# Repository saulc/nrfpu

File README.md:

# nrfpu
eagle pcb for atmega328p pu and nrf24l01+

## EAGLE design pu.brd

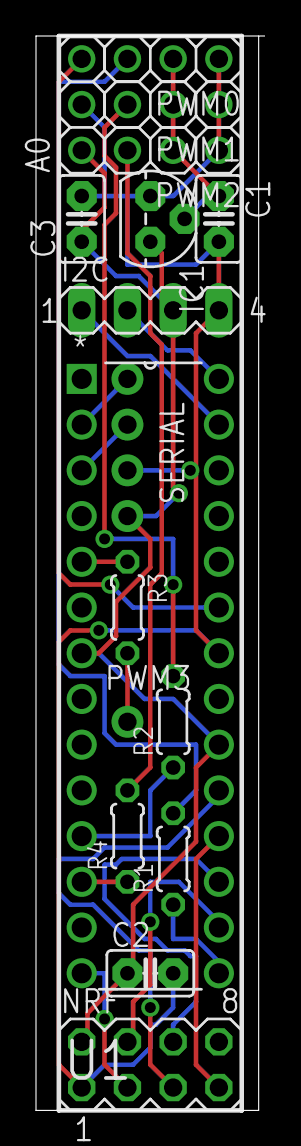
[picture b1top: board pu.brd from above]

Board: 2 copper layers, 12.7 x 59.7 mm, 17 parts (0 on the bottom side), 21 nets.

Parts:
A0: 1X03
C1, C2: 1uf; C025-025X050
C3: 10uf; C025-025X050
I2C: MA04-1
IC1: TO92
NRF: MA04-2
PWM0, PWM1, PWM2: 1X03
PWM3: 1X01-CLEANBIG
R1, R2, R3, R4: 0204/5
SERIAL: 1X4-CLEANBIG; 1X04-CLEANBIG
U1: ATMEGA328P-PU; DIP254P762X457-28

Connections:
3PWM: R3.1, U1.5
5PWM: R2.1, U1.11
6PWM: R4.1, U1.12
9PWM: R1.1, U1.15
10PWM: NRF.4, U1.16
A0: A0.3, U1.23
D8: NRF.3, U1.14
GND: A0.2, C1.2, C2.2, C3.2, I2C.4, IC1.1, NRF.1, PWM0.1, PWM1.1, PWM2.1, SERIAL.3, U1.22
MISO: NRF.7, U1.18
MOSI: NRF.6, U1.17
PWM0OUT: PWM0.3, R1.2
PWM1OUT: PWM1.3, R2.2
PWM2OUT: PWM2.3, R4.2
PWM3OUT: PWM3.1, R3.2
RX: SERIAL.1, U1.2
SCK: NRF.5, U1.19
SCL: I2C.2, U1.28
SDA: I2C.1, U1.27
TX: SERIAL.2, U1.3
VCC: A0.1, C2.1, C3.1, I2C.3, IC1.3, NRF.2, SERIAL.4, U1.7, U1.20
VIN: C1.1, IC1.2, PWM0.2, PWM1.2, PWM2.2

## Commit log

2017-05-03 first
    upload
2017-05-03 upload images
    pcb render from oshpark
